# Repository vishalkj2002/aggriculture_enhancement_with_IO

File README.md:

# agriculture_enhancement_with_IO

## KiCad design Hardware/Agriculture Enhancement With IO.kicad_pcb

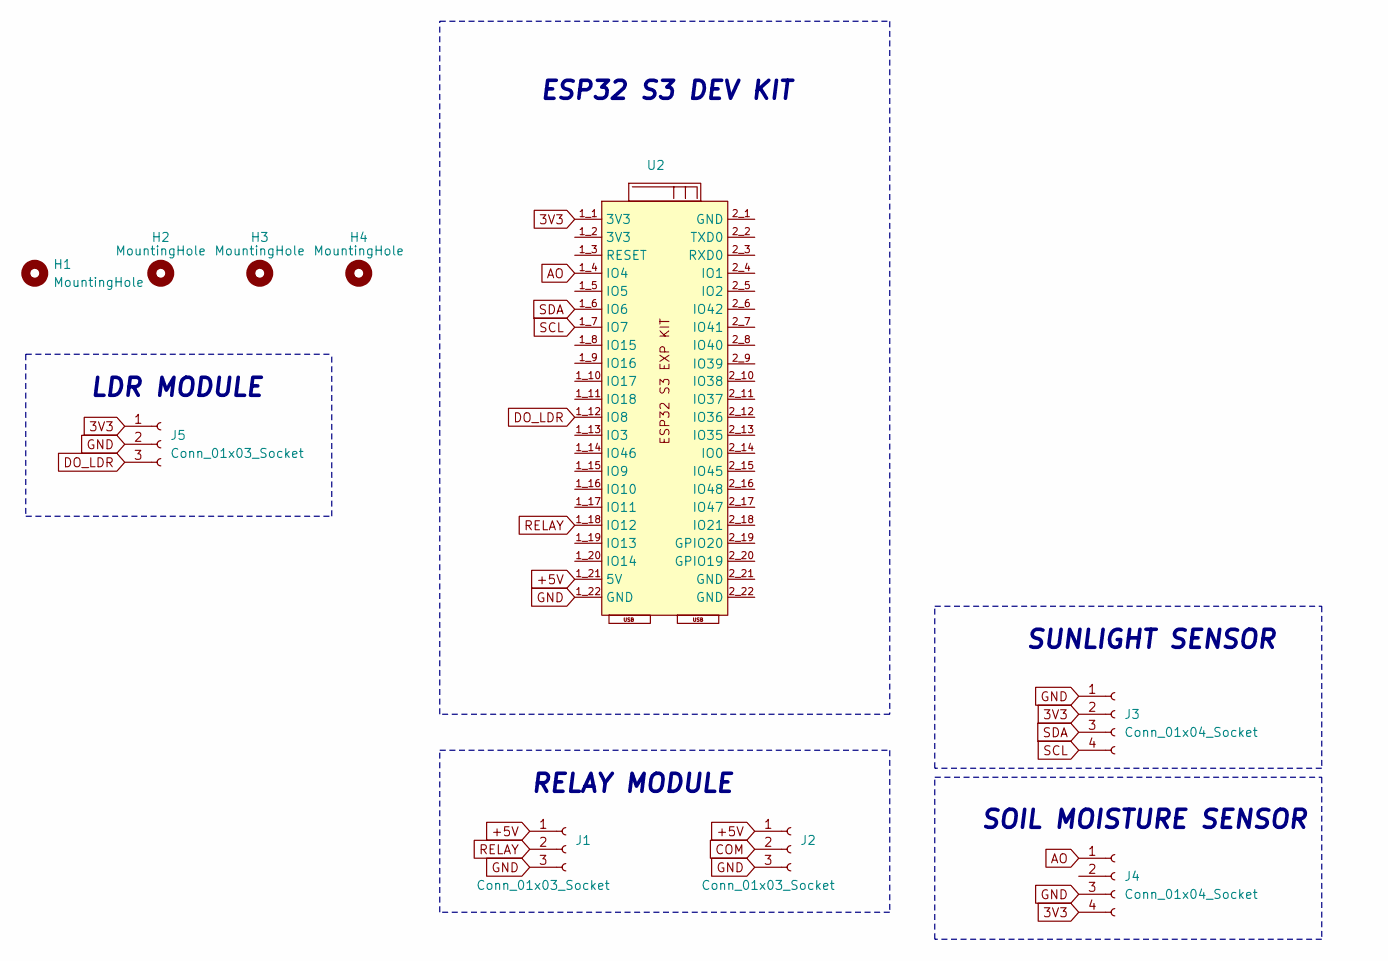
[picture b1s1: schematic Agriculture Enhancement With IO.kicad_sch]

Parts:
H1, H2, H3, H4: MountingHole; MountingHole_3.2mm_M3
J1, J5: Conn_01x03_Socket; PinHeader_1x03_P2.54mm_Vertical
J2: Conn_01x03_Socket; TerminalBlock_bornier-3_P5.08mm
J3: Conn_01x04_Socket; JST_XH_B4B-XH-A_1x04_P2.50mm_Vertical
J4: Conn_01x04_Socket; PinHeader_1x04_P2.54mm_Vertical
U2: ESP32-S3BRD

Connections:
3V3: J3.2, J4.4, J5.1, U2.1_1 (3V3)
+5V: J1.1, J2.1, U2.1_21 (5V)
AO: J4.1, U2.1_4 (IO4)
COM: J2.2
DO_LDR: J5.3, U2.1_12 (IO8)
GND: J1.3, J2.3, J3.1, J4.3, J5.2, U2.1_22 (GND)
RELAY: J1.2, U2.1_18 (IO12)
SCL: J3.4, U2.1_7 (IO7)
SDA: J3.3, U2.1_6 (IO6)

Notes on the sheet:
SOIL MOISTURE SENSOR
LDR MODULE
ESP32 S3 DEV KIT
SUNLIGHT SENSOR
RELAY MODULE

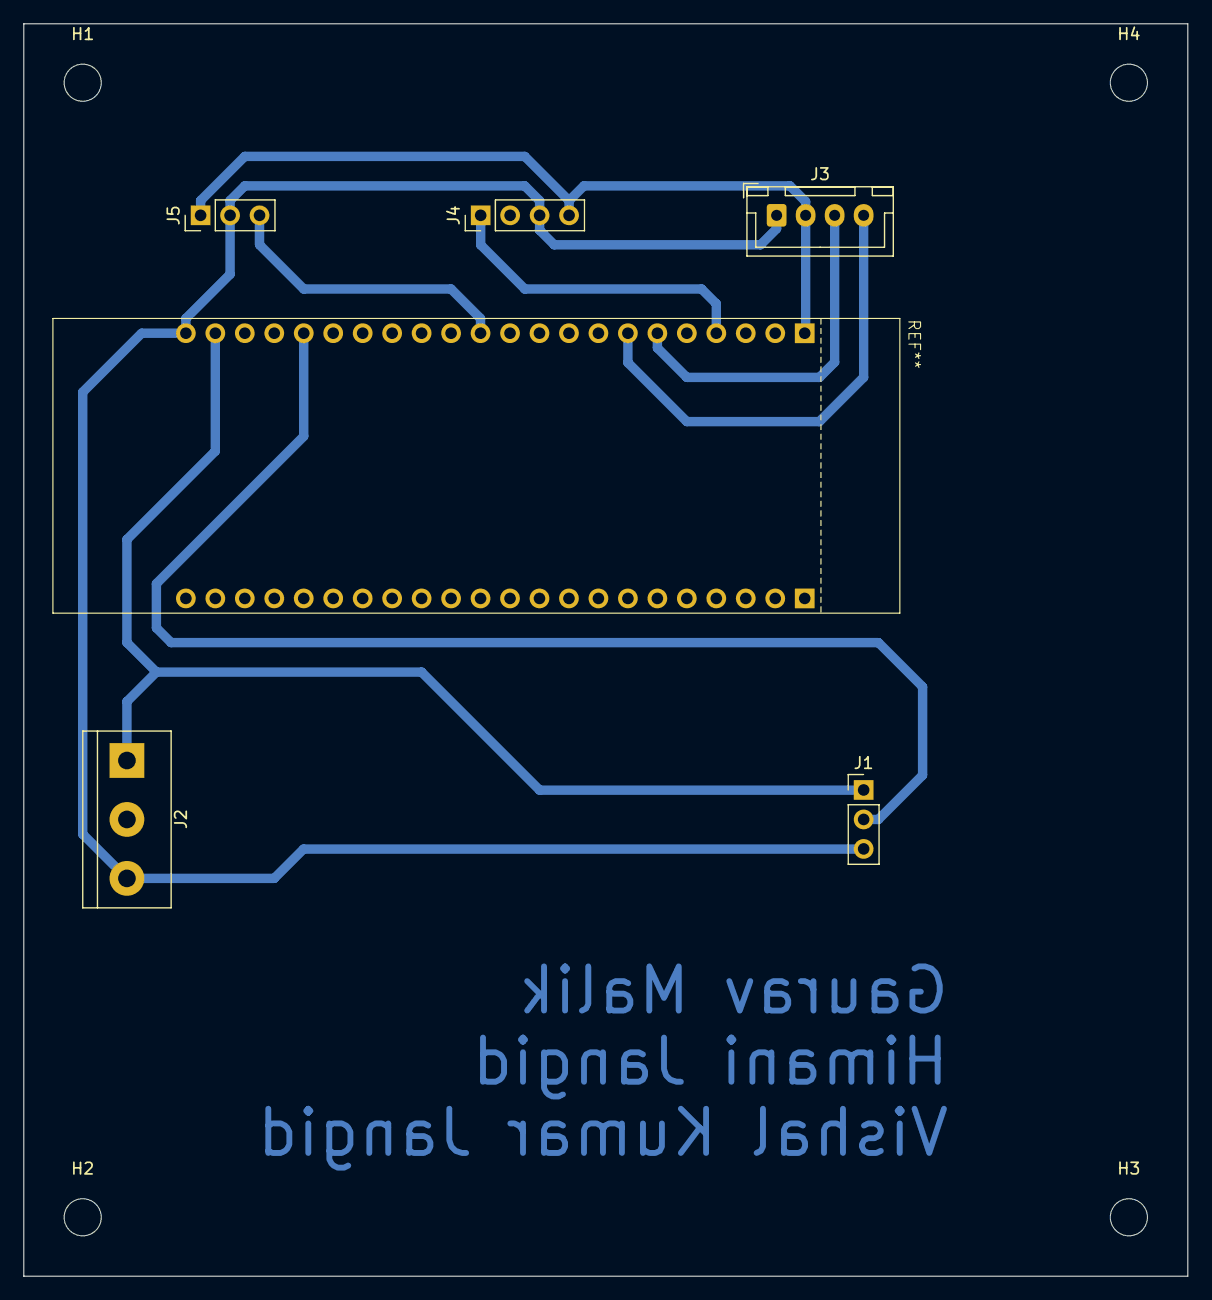
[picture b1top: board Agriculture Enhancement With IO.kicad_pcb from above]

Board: 2 copper layers, 100.3 x 108.0 mm, 10 parts (0 on the bottom side), 8 nets.

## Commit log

2023-09-01 Added project files
